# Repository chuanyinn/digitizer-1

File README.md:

# Digitzer
[Hardware](https://github.com/nupole/digitizer/tree/rev/hw) and [firmware](https://github.com/nupole/digitizer/tree/rev/fw) prototyping of a multichannel 8-bit, 100 MS/s digitizer.

## Features
- Two 1 V<sub>pp</sub> single-ended input channels
- Analog band-pass of 10 kHz to 10 MHz
- 8-bit, 100 MS/s ADCs
- Reconfigurable FPGAa
 - 1 kB/channel event buffer
 - Programmable pre and post-trigger sizes (0 to 2.55 &mu;s)
 - Programmable channel trigger thresholds
 - Programmable coincidence window sizes (0 to 2.55 &mu;s)
 - Programmable trigger coincidence value
 - Programmable trigger veto window size (0 to 2.55 &mu;s)
 - 32 I/O connections
 - 1 single-ended coax I/O
 - 4 JTAG connections

## Table of Contents
1. [Features](#features)
2. [Overview](#overview)

## Overview
The digitizer is a 100 mm by 50 mm electronics card with two 1 V<sub>pp</sub> single-ended input channels sampled by an 8-bit, 100 MS/s ADC. Each channels incoming data is written into its own circular buffer, and upon an internal trigger, is block transferred into its own 1 kB event buffer using user-defined pre and post-trigger window sizes ranging from 0 to 2.55 microseconds (0 to 255 bytes respectively). The event buffers are then readout on a parallel backplane interface.

To form an internal coincidence trigger, each input channel generates a user-defined coincidence window (ranging in size from 0 to 2.55 microseconds) by comparing the current ADC sample with a user-defined threshold. These coincidence windows are added and compared with a user-defined coincidence value to generate both a trigger and veto window. The veto window has user-defined size ranging from 0 to 2.55 microseconds and prevents a re-trigger during its duration.

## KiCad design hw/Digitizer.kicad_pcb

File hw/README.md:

# Digitizer (Hardware)
[Hardware](https://github.com/nupole/digitizer/tree/rev/hw) prototyping of a multichannel 8-bit, 100 MS/s digitizer.

## Features
 - Two singled ended input channels
 - Low-pass filter designed using current feedback amplifier in a Sallen-Key topology
 - 8-bit, 100 MS/s ADCs
 - Reconfigurable FPGA
  - 32 I/O connections
  - 1 single-ended coax I/O
  - 4 JTAG connections

## Modifications for Rev 0.1
 - [ ] Remove the solder mask covering the analog and trigger inputs
 - [ ] Exchange 4 pin header for a 6 pin header to include 3.3 V and GND from JTAG programmer
 - [ ] Copper fill the entire power plane
 - [ ] Add grounding strips on the front and back copper layers
 - [ ] Remove unused copper trace on the back copper layers
 - [ ] Slow the TCLK from FT232H programmer by bypassing to ground with 10's of pF

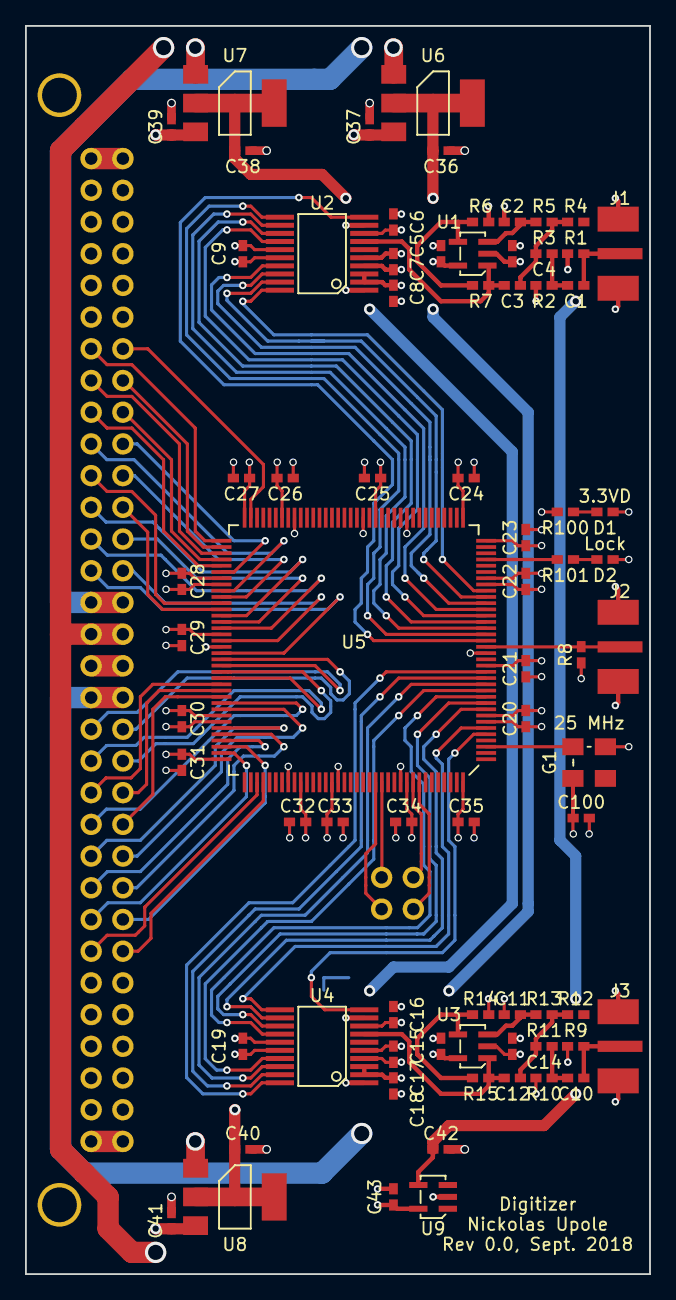
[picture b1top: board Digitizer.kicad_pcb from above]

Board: 4 copper layers, 50.0 x 100.0 mm, 77 parts (0 on the bottom side), 81 nets.

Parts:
C1, C10: 1u; 0402
C2, C3, C4, C5, C6, C7, C8, C9, C11, C12, C14, C15, C16, C17, C18, C19, C20, C21, C22, C23, C24, C25, C26, C27, C28, C29, C30, C31, C32, C33, C34, C35, C36, C37, C38, C39, C40, C41, C42, C43, C100: C; 0402
D1, D2: LED; 0402
G1: 510CBA25M0000BAGR; OSC
J1, J2, J3: SMA
J7: Conn_x4; Conn_x4_Straight
J10: Conn_x64; Conn_x64_RightAngle
R1, R2, R8, R9, R10: 50; 0402
R3, R4, R5, R6, R7, R11, R12, R13, R14, R15, R100, R101: R; 0402
U1, U3: AD8014; SOT-23-5
U2, U4: AD9283; SSOP-20
U5: MachXO2; TQFP-144
U6, U7, U8: NCP1117; SOT-223
U9: MIC5270; SOT-23-5

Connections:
/3.3VA: C6.1, C7.1, C16.1, C17.1, C38.1, U2.5, U2.8, U4.5, U4.8, U7.2
/3.3VD: C9.2, C19.2, C20.1, C21.1, C22.1, C23.1, C24.1, C25.1, C26.1, C27.1, C28.2, C29.2, C30.2, C31.2, C32.2, C33.2, C34.2, C35.2, C40.1, C100.1, D1.2, G1.4, U2.15, U4.15, U5.7, U5.16, U5.30, U5.36, U5.37, U5.51, U5.66, U5.72, U5.79, U5.88, U5.102, U5.108, U5.118, U5.123, U5.135, U5.144, U8.2
/5V: C39.1, C41.1, J10.17, J10.48, U7.3, U8.3
/5VA: C5.1, C15.1, C36.1, U1.5, U3.5, U6.2
/12V: C37.1, J10.18, J10.47, U6.3
/25MHz: G1.3, U5.3
/-5VA: C4.2, C14.2, C42.2, U1.2, U3.2, U9.4
/-12V: C43.2, J10.15, J10.50, U9.5
/BP_D0: J10.39, U5.71
/BP_D1: J10.40, U5.74
/BP_D2: J10.41, U5.76
/BP_D3: J10.42, U5.78
/BP_D4: J10.43, U5.82
/BP_D5: J10.44, U5.84
/BP_D6: J10.45, U5.86
/BP_D7: J10.46, U5.89
/BP_D8: J10.51, U5.92
/BP_D9: J10.52, U5.94
/BP_D10: J10.53, U5.97
/BP_D11: J10.54, U5.98
/BP_D12: J10.55, U5.100
/BP_D13: J10.56, U5.104
/BP_D14: J10.57, U5.106
/BP_D15: J10.58, U5.112
/GND: C2.2, C4.1, C5.2, C6.2, C7.2, C8.2, C9.1, C11.2, C14.1, C15.2, C16.2, C17.2, C18.2, C19.1, C20.2, C21.2, C22.2, C23.2, C24.2, C25.2, C26.2, C27.2, C28.1, C29.1, C30.1, C31.1, C32.1, C33.1, C34.1, C35.1, C36.2, C37.2, C38.2, C39.2, C40.2, C41.2, C42.1, C43.1, C100.2, D2.1, G1.2, J1.1, J1.3, J1.4, J1.5, J2.1, J2.3, J2.4, J2.5, J3.1, J3.3, J3.4, J3.5, J10.1, J10.16, J10.32, J10.33, J10.49, J10.64, R1.2, R2.2, R6.1, R8.2, R9.2, R10.2, R14.1, R100.1, U2.1, U2.4, U2.9, U2.16, U4.1, U4.4, U4.9, U4.16, U5.8, U5.18, U5.29, U5.46, U5.53, U5.64, U5.80, U5.90, U5.101, U5.116, U5.124, U5.134, U6.1, U7.1, U8.1, U9.2
/IO7: J10.7, U5.111
/IO8: J10.8, U5.107
/IO9: J10.9, U5.105
/IO10: J10.10, U5.103
/IO11: J10.11, U5.99
/IO12: J10.12, U5.96
/IO13: J10.13, U5.95
/IO14: J10.14, U5.93
/IO19: J10.19, U5.91
/IO20: J10.20, U5.87
/IO21: J10.21, U5.85
/IO22: J10.22, U5.83
/IO23: J10.23, U5.81
/IO24: J10.24, U5.77
/IO25: J10.25, U5.75
/IO26: J10.26, U5.73
/LOCK: R101.2, U5.33
/Sig1: C3.2, R7.2, U1.1, U2.7
/Sig1_CLK: U2.10, U5.20
/Sig1_D0: U2.20, U5.28
/Sig1_D1: U2.19, U5.27
/Sig1_D2: U2.18, U5.26
/Sig1_D3: U2.17, U5.25
/Sig1_D4: U2.14, U5.24
/Sig1_D5: U2.13, U5.23
/Sig1_D6: U2.12, U5.22
/Sig1_D7: U2.11, U5.21
/Sig2: C12.2, R15.2, U3.1, U4.7
/Sig2_CLK: U4.10, U5.5
/Sig2_D0: U4.20, U5.15
/Sig2_D1: U4.19, U5.14
/Sig2_D2: U4.18, U5.13
/Sig2_D3: U4.17, U5.12
/Sig2_D4: U4.14, U5.11
/Sig2_D5: U4.13, U5.10
/Sig2_D6: U4.12, U5.9
/Sig2_D7: U4.11, U5.6
/TCK: J7.3, U5.131
/TDI: J7.2, U5.136
/TDO: J7.1, U5.137
/TMS: J7.4, U5.130
/Trig: J2.2, R8.1, U5.19
unnamed: C1.1, J1.2, R1.1
unnamed: C1.2, R2.1, R3.1
unnamed: C2.1, R5.2, U1.3
unnamed: C3.1, R3.2, R4.2, R5.1
unnamed: C8.1, U2.2, U2.3
unnamed: C10.1, J3.2, R9.1
unnamed: C10.2, R10.1, R11.1
unnamed: C11.1, R13.2, U3.3
unnamed: C12.1, R11.2, R12.2, R13.1
unnamed: C18.1, U4.2, U4.3
unnamed: D1.1, R100.2
unnamed: D2.2, R101.1
unnamed: R6.2, R7.1, U1.4
unnamed: R14.2, R15.1, U3.4

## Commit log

2018-11-20 Initial commit of TRIGMGR (trigmgr.vhdl)
    Added a TRIGMGR (trigmgr.vhdl) composed of the following entities:
    - COINWIN (coinwin.vhdl): generates a user-defined coincidence window
    when the ADC value reads below a user-defined threshold
    - COINDETR (coindetr.vhdl): generates a 1 clock cycle pulse when a
    user-defined number of coincidence windows overlap
    - TRIG (trig.vhdl): generates a 1 clock cycle pulse and a user defined
2018-11-20 Initial commit of clock manager (clkmgr.vhdl)
    The clock manager uses the EHXPLLJ component from the MachXO2 library
2018-11-20 Initial commit of DIGITIZER (digitizer.vhdl)
2018-11-23 Initial commit of BPIF (bpif.vhdl), clean up of files for synthesis
    Created a backplane interface (BPIF) for initial testing of the trigger
    manager
    - Read and write commands use 1-bit
    - Addressing uses a 6-bit parallel interface
    Only 7 registers so use 3 LSBs
    - Data uses an 8-bit parallel interface
2018-11-27 Initial hardware commit
    The hardware commit contains the following useful items
    - Vendor datasheets and documentation pertaining to both firmware and hardware
    - KiCad source files including schematic and footprint libraries
    - LTSpice simulation files for an estimate of the analog front end bandwidth (from Bode plot)
2018-11-27 Initial commit of channel manager (CHMGR.vhdl)
    The intial commit for the channel manager includes its dependencies on
    the following modules:
    - Add2: adds 2 2-bit numbers
    - Add10: adds 2 10-bit numbers in a pipeline
    - UCNT: loadable up counter
2018-11-28 Initial commit of some sparse README.md files
